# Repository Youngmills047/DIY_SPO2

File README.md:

# DIY_SPO2
DIY SpO₂ and Heart Rate Monitor

This project is a DIY pulse oximeter built around the MAX30102 sensor, Arduino Nano, and an SSD1306 OLED display.
It measures blood oxygen saturation (SpO₂) and heart rate (BPM) in real-time.

The repository includes:

Firmware (Arduino code)

Hardware (KiCad schematic & PCB)

Documentation (wiring diagrams, PCB images, BOM, etc.)

🚀 Features

Reads SpO₂ (%) and heart rate (BPM) using the MAX30102 sensor

Real-time display on 0.96" SSD1306 OLED screen

Compact PCB design (KiCad project + Gerbers included)

Open-source and customizable

🛠 Components Used

Arduino Nano (ATmega328P)

MAX30102 Pulse Oximeter & Heart Rate Sensor

SSD1306 OLED Display (128x64, I2C)

Misc: Resistors, capacitors, push buttons, connectors

🔧 Getting Started

1️⃣ Clone the Repository

https://github.com/Youngmills047/DIY_SPO2.git

2️⃣ Install Arduino Libraries

Adafruit SSD1306

Adafruit GFX

MAX3010x (SparkFun library)

You can install them via Arduino IDE → Tools → Manage Libraries.

3️⃣ Upload the Firmware

Open spo2.ino in Arduino IDE

Select Arduino Nano and correct COM port

Upload the code

4️⃣ Hardware Setup

Connect MAX30102 → I2C pins (A4 = SDA, A5 = SCL)

Connect SSD1306 OLED → I2C pins (same bus)

Power from USB or regulated 5V

📐 Hardware (KiCad)

The full PCB design is available in /hardware/.

Open .kicad_pro in KiCad

Gerber files are in /exports/gerbers/ (ready for fabrication)

BOM file is included

⚠️ Disclaimer

This project is for educational purposes only.
It is not a medical-grade device and should not be used for diagnosis or treatment.

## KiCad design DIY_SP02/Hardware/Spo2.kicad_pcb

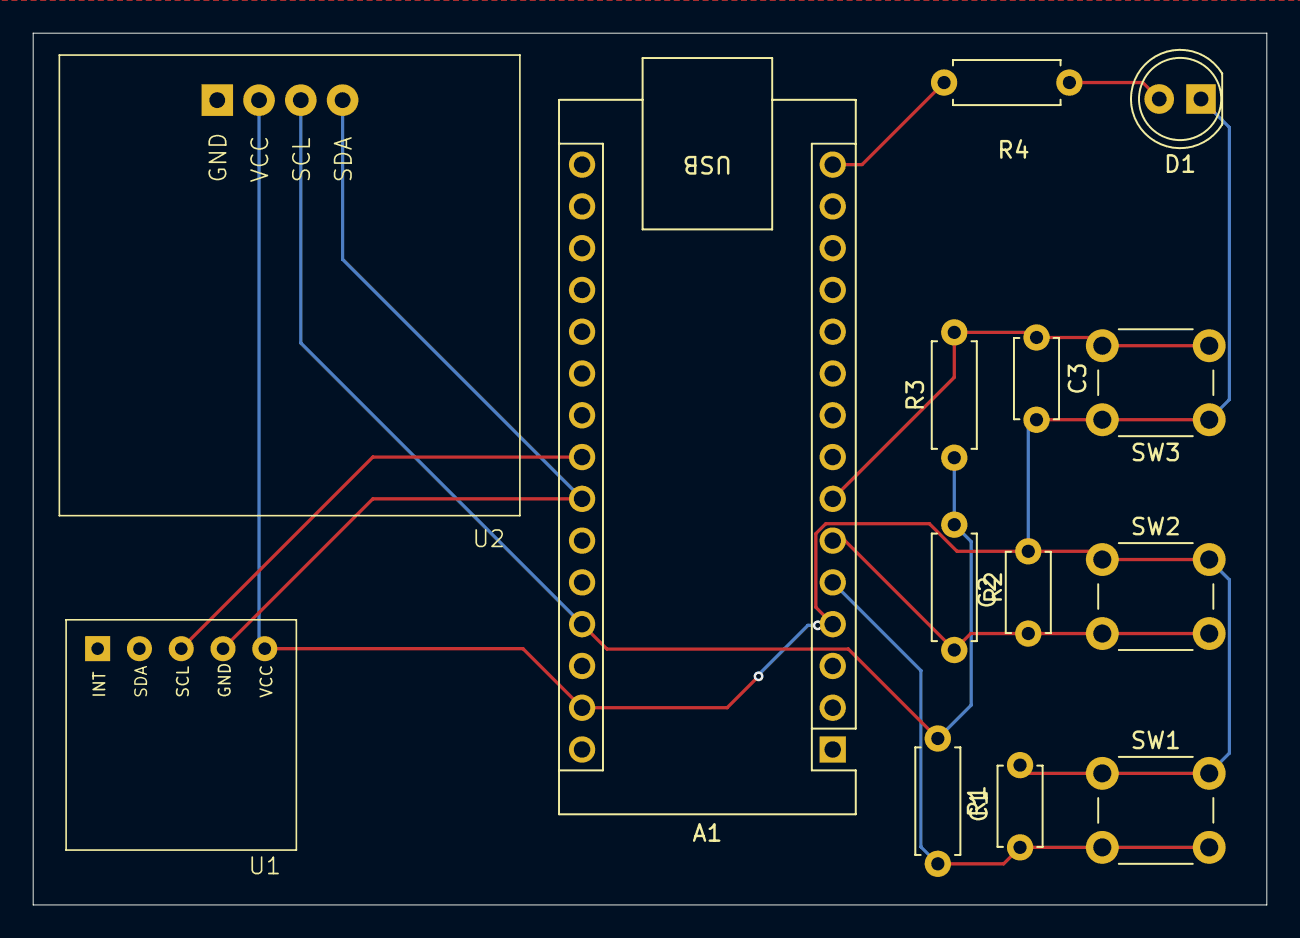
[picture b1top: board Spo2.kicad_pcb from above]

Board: 4 copper layers, 75.0 x 53.0 mm, 14 parts (0 on the bottom side), 9 nets.

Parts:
A1: Arduino_Nano_v3.x; Arduino_Nano
C1, C2, C3: 100n; C_Disc_D4.7mm_W2.5mm_P5.00mm
D1: LED; LED_D5.0mm
R1, R2, R3, R4: 1k; R_Axial_DIN0207_L6.3mm_D2.5mm_P7.62mm_Horizontal
SW1, SW2, SW3: SW_Push; SW_PUSH_6mm
U1: MAX3012; MAX3012-MOD
U2: SSD1306

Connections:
+5V: A1.27 (+5V), R1.1, R2.1, R3.1, U2.2 (VCC)
GND: A1.4 (GND), A1.29 (GND), C1.2, C2.2, C3.2, D1.1 (K), SW1.1, SW2.1, SW3.1, U1.4 (GND), U2.1 (GND)
unnamed: A1.23 (A4), U1.2 (SDA)
unnamed: A1.24 (A5), U1.3 (SPL), U2.3 (SCL)
unnamed: A1.5 (D2), C1.1, R1.2, SW1.2
unnamed: A1.6 (D3), C2.1, R2.2, SW2.2
unnamed: A1.7 (D4), C3.1, R3.2, SW3.2
unnamed: A1.15 (D12), R4.1
unnamed: D1.2 (A), R4.2
